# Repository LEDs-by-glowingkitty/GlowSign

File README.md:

## Warning:

This project is currently under active development and has not been fully tested yet. If you decide to build or clone the project, be aware it might not work yet as expected. Use at your own risk.

## What is this project?

A battery powered LED sign for your laptop, or where ever else you want to use it!

## Links

- [Main PCB files](https://github.com/glowingkitty/GlowKittySign/tree/main/Main%20PCB)
- [Aluminum Cover PCB - Cat Edition files](https://github.com/glowingkitty/GlowKittySign/tree/main/AluminumCover%20PCB%20cat%20edition)

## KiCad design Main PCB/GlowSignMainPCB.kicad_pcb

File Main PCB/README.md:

# GlowSign Main PCB

The main PCB for GlowSign. With all the LEDs, the integrated ESP32, a microphone to make the LED animations react to music - and it runs GlowOS (my WLED fork). But you can also upload your own software to the ESP32. The PCB can be powered via USB-C and via a lipo battery.

## Links

- [Schematic](https://github.com/glowingkitty/GlowSign/blob/main/Main%20PCB/GlowSignMainPCB.pdf)
- [Interactive BOM](https://htmlpreview.github.io/?https://github.com/glowingkitty/GlowSign/blob/main/Main%20PCB/bom/ibom.html)

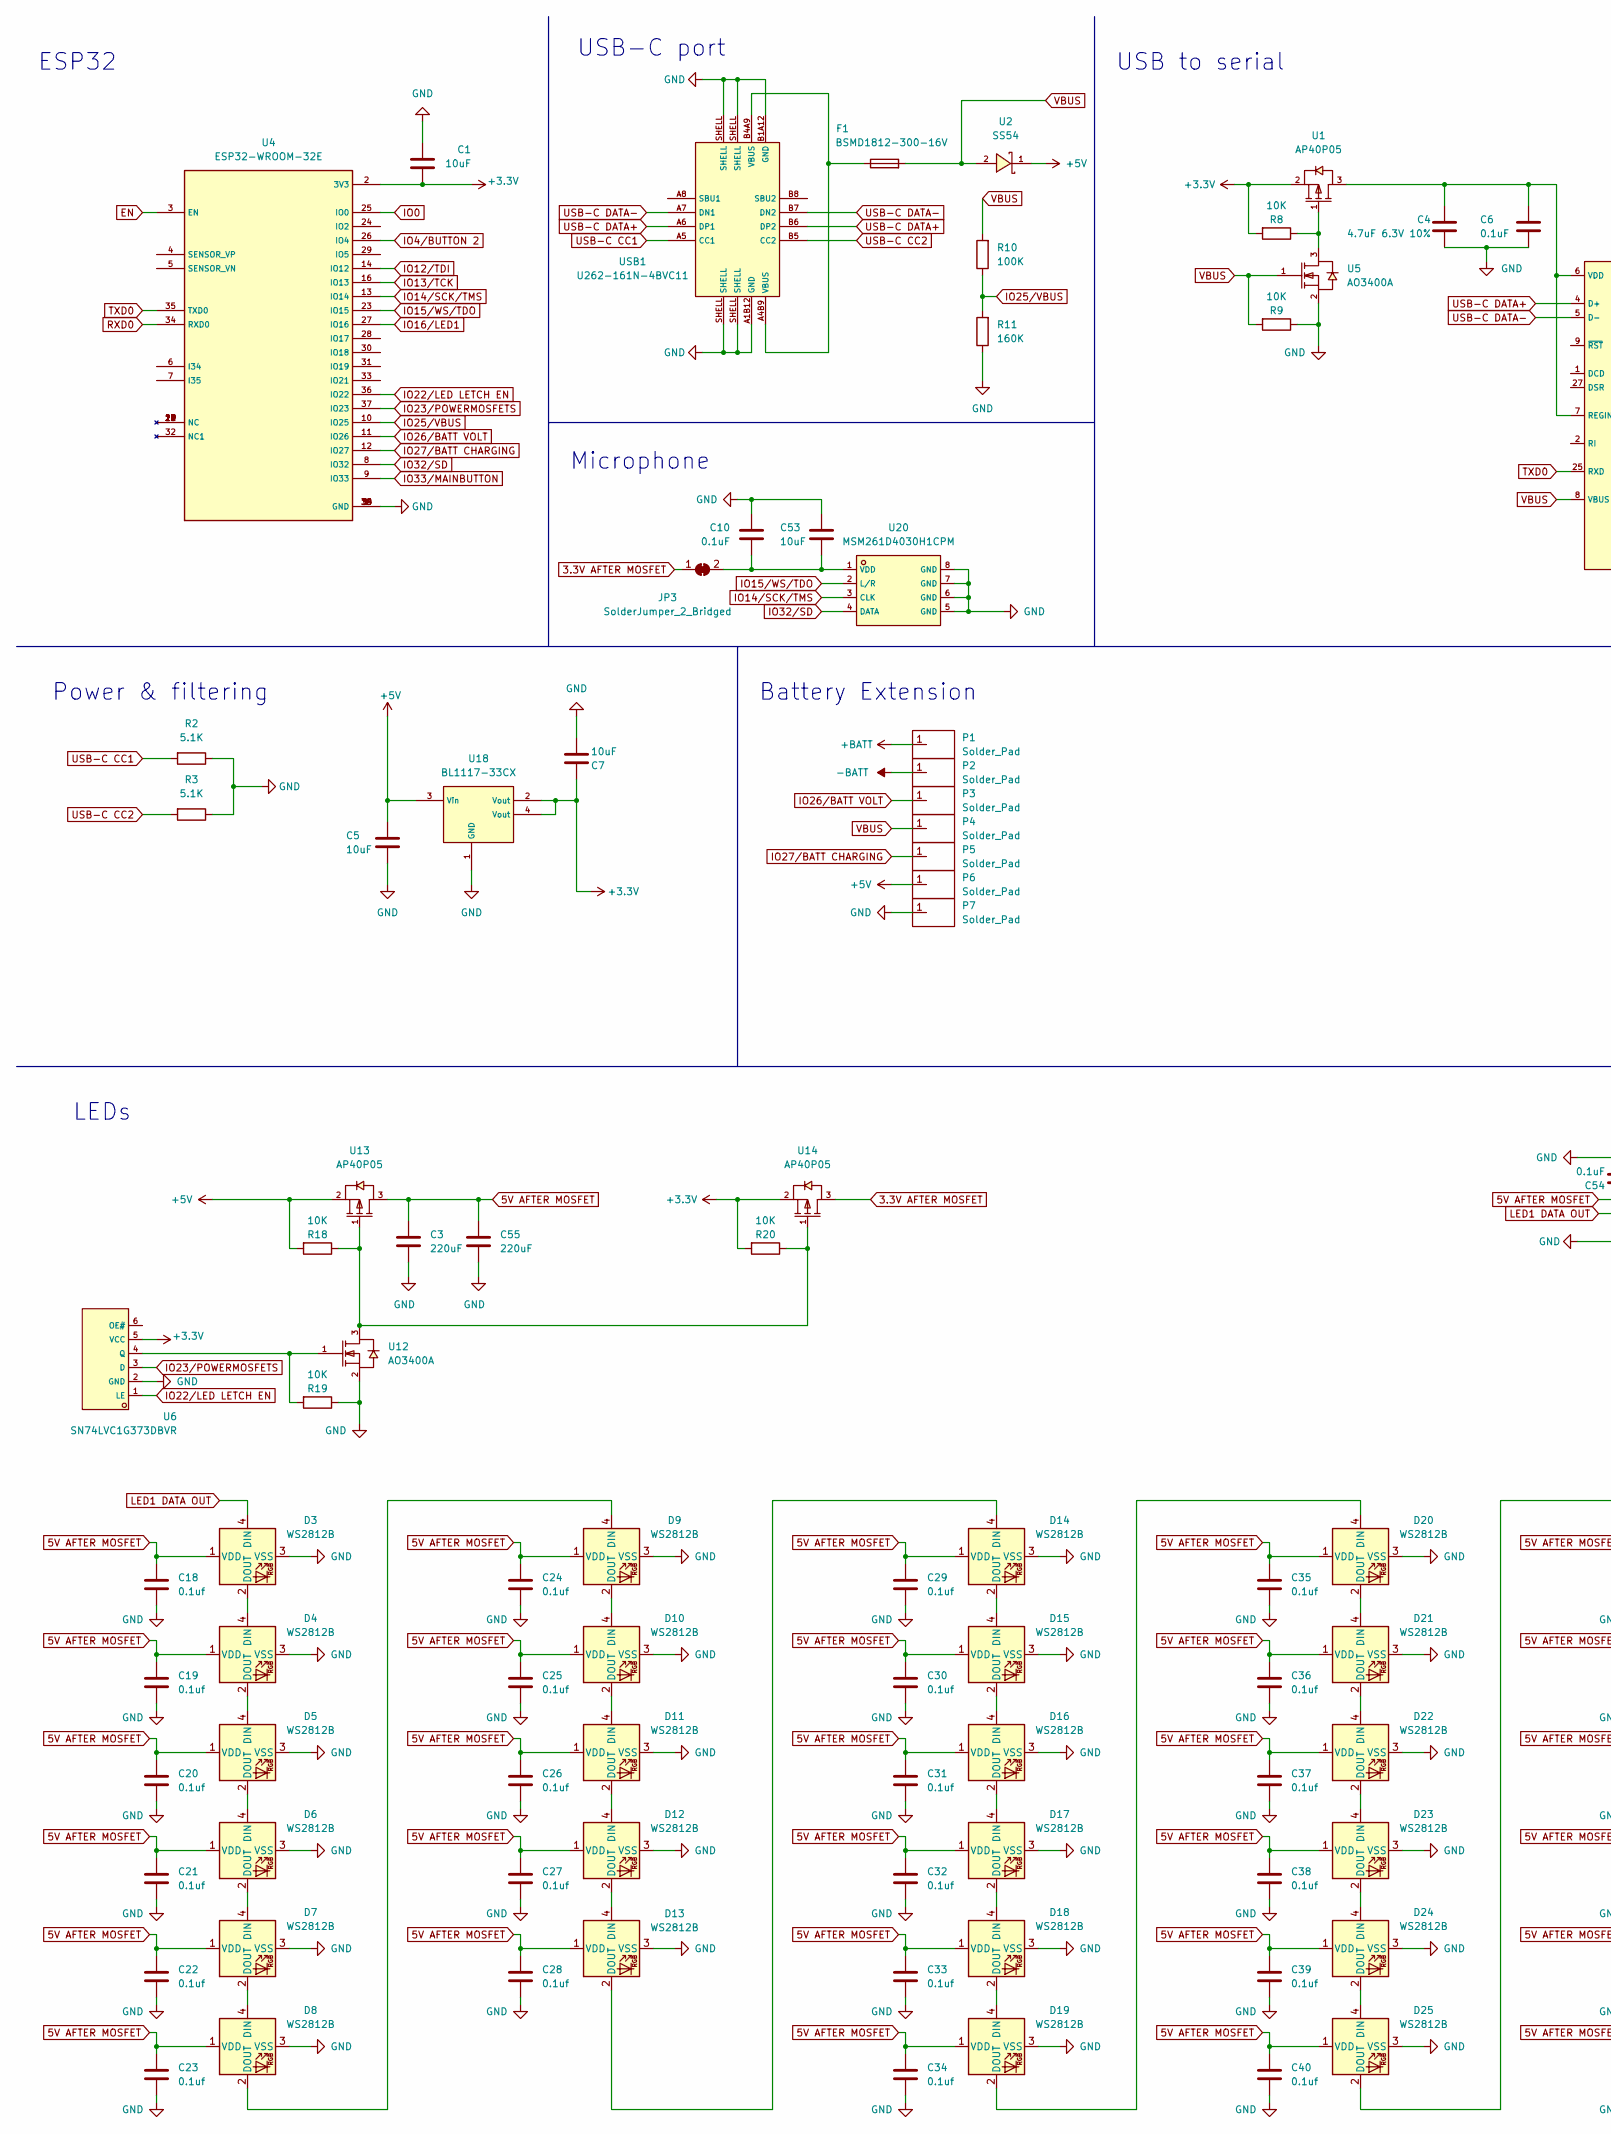
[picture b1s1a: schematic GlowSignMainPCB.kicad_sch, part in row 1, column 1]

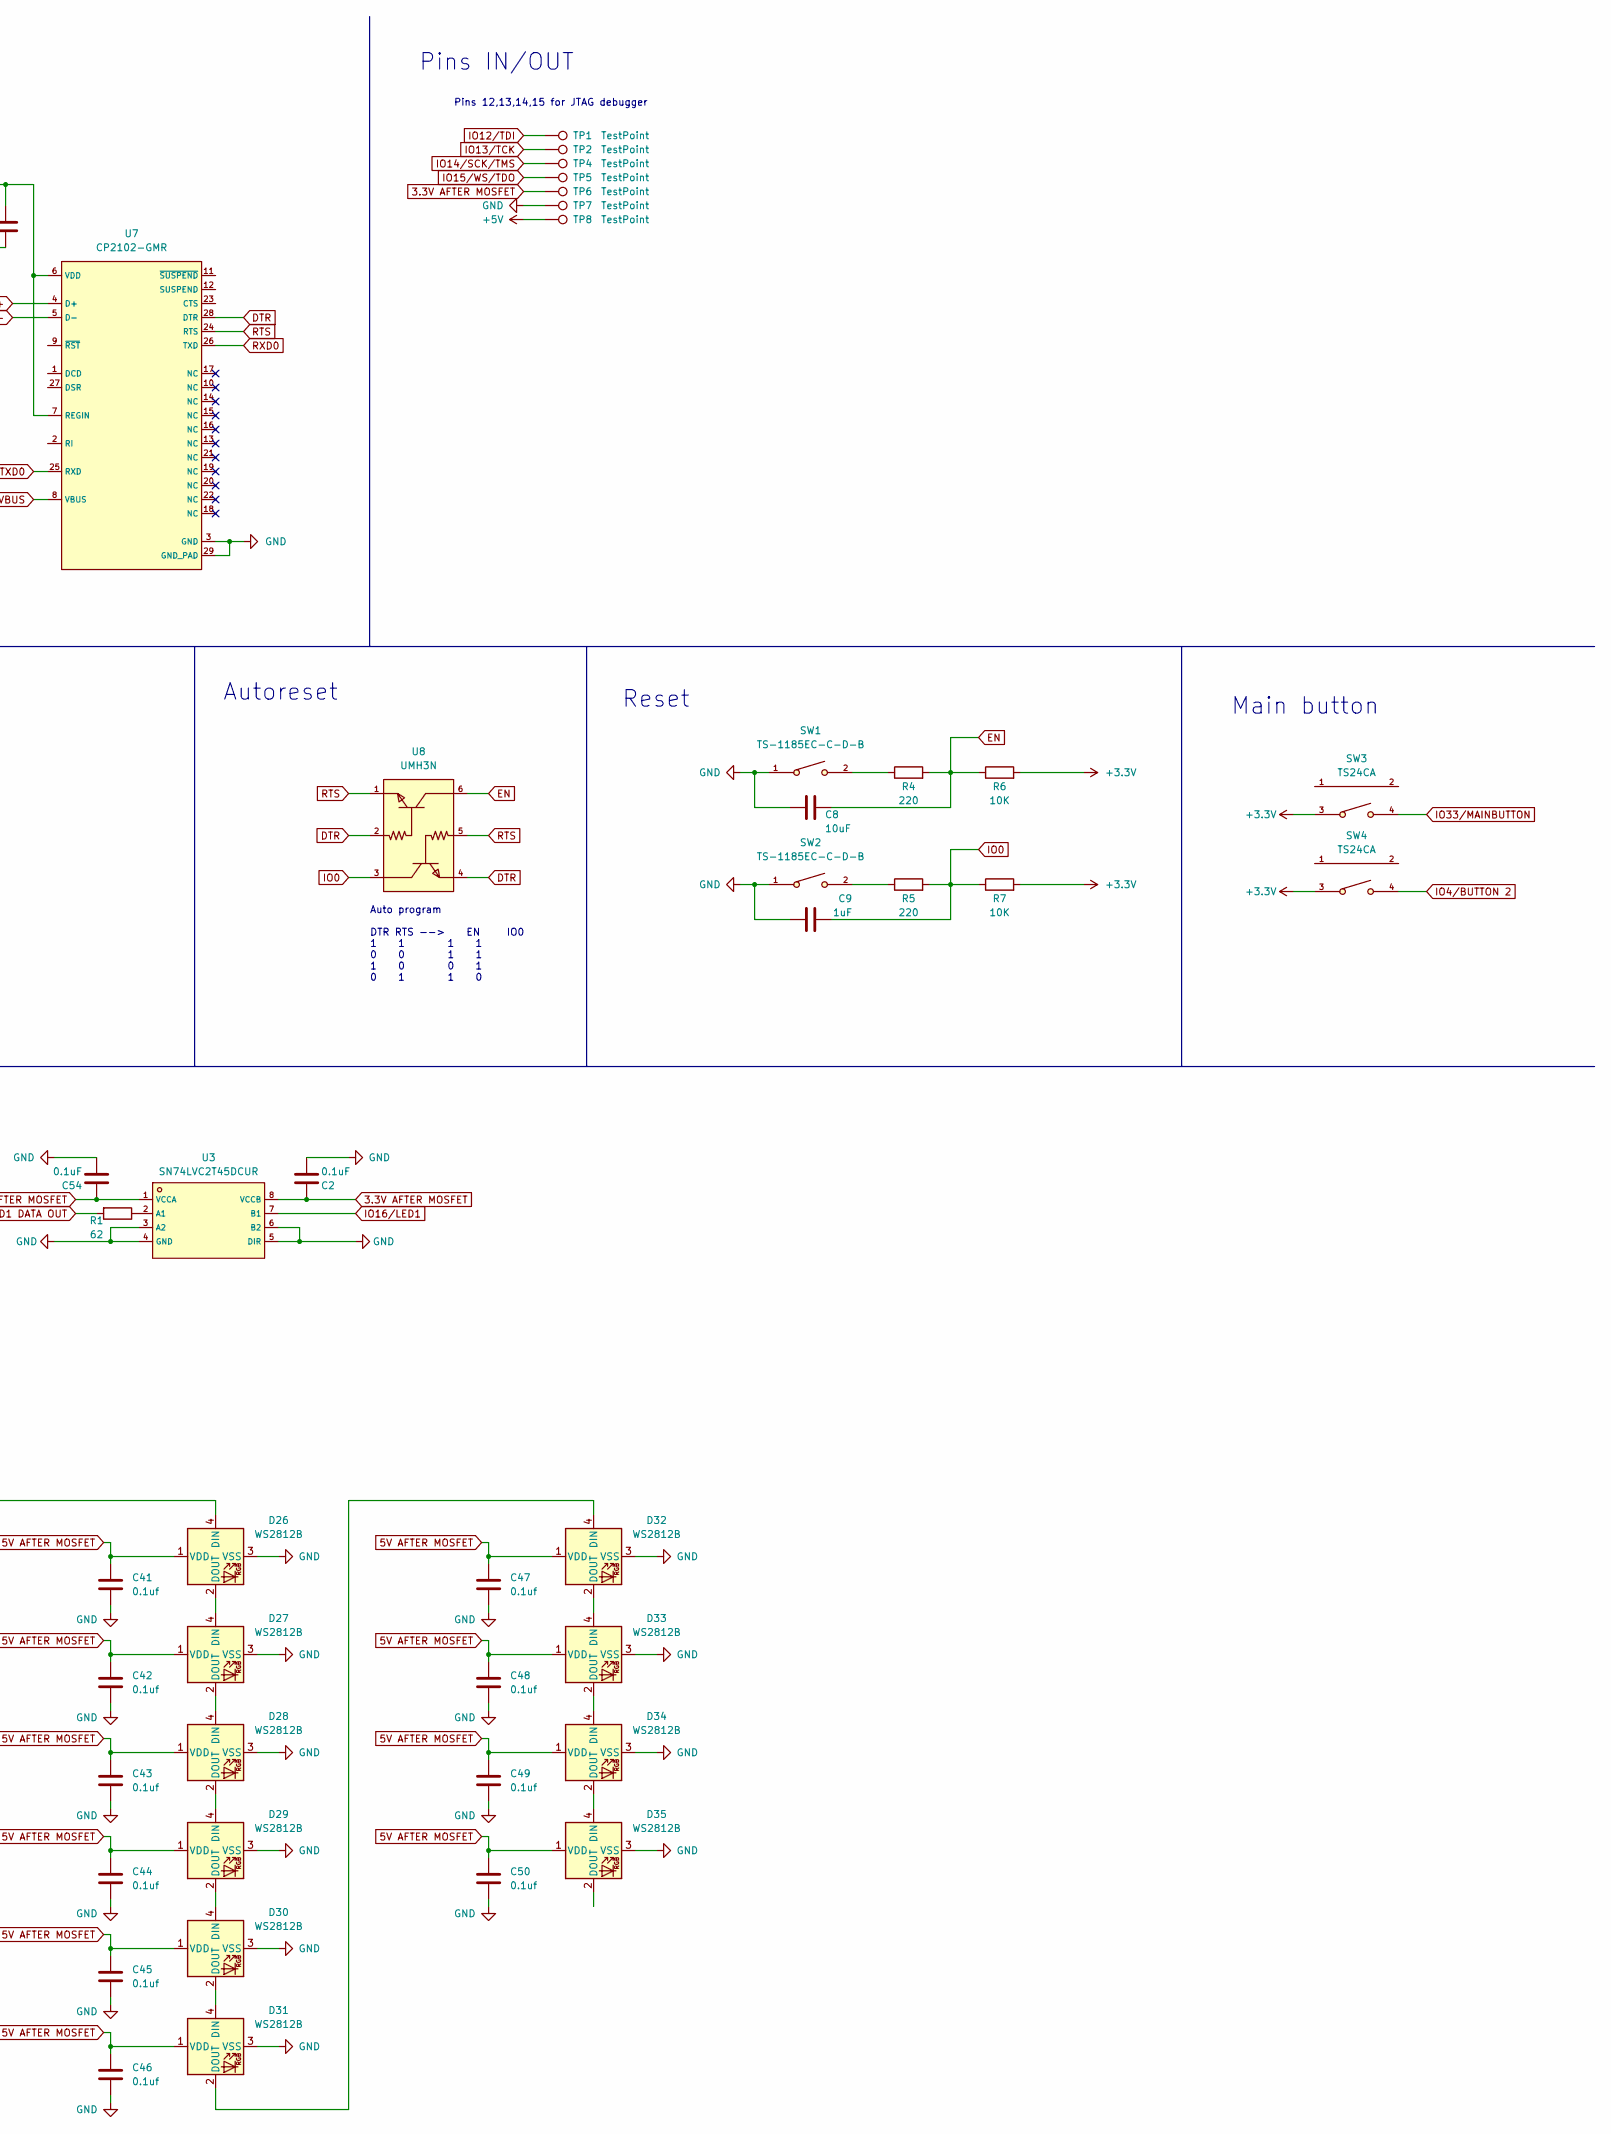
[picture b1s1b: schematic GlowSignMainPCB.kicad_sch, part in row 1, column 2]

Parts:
C1, C5, C7, C8, C53: 10uF; C_0603_1608Metric_Pad1.08x0.95mm_HandSolder; LCSC # C19702
C2, C6, C10, C54: 0.1uF; C_0603_1608Metric_Pad1.08x0.95mm_HandSolder; LCSC # C14663
C3, C55: 220uF; C_1206_3216Metric_Pad1.33x1.80mm_HandSolder; LCSC # C412252
C4: 4.7uF 6.3V 10%; C_0603_1608Metric_Pad1.08x0.95mm_HandSolder; LCSC # C19666
C9: 1uF; C_0603_1608Metric_Pad1.08x0.95mm_HandSolder; LCSC # C15849
C18, C19, C20, C21, C22, C23, C24, C25, C26, C27, C28, C29, C30, C31, C32, C33, C34, C35, C36, C37, C38, C39, C40, C41, C42, C43, C44, C45, C46, C47, C48, C49, C50: 0.1uf; C_0603_1608Metric_Pad1.08x0.95mm_HandSolder; LCSC # C14663
D3, D4, D5, D6, D7, D8, D9, D10, D11, D12, D13, D14, D15, D16, D17, D18, D19, D20, D21, D22, D23, D24, D25, D26, D27, D28, D29, D30, D31, D32, D33, D34, D35: WS2812B; LED_WS2812B_PLCC4_5.0x5.0mm_P3.2mm; LCSC # C2843785
F1: BSMD1812-300-16V; Fuse_1812_4532Metric_Pad1.30x3.40mm_HandSolder; LCSC # C883162
JP3: SolderJumper_2_Bridged; SolderJumper-2_P1.3mm_Bridged_RoundedPad1.0x1.5mm
P1, P2, P3, P4, P5, P6, P7: Solder_Pad; Solder pad
R1: 62; R_0603_1608Metric_Pad0.98x0.95mm_HandSolder; LCSC # C177352
R2, R3: 5.1K; R_0603_1608Metric_Pad0.98x0.95mm_HandSolder; LCSC # C23186
R4, R5: 220; R_0603_1608Metric_Pad0.98x0.95mm_HandSolder; LCSC # C22962
R6, R7, R8, R9, R18, R19, R20: 10K; R_0603_1608Metric_Pad0.98x0.95mm_HandSolder; LCSC # C25804
R10: 100K; R_0603_1608Metric_Pad0.98x0.95mm_HandSolder; LCSC # C25803
R11: 160K; R_0603_1608Metric_Pad0.98x0.95mm_HandSolder; LCSC # C22813
SW1, SW2: TS-1185EC-C-D-B; SW-SMD_4P-L3.7-W3.0-P1.50-LS4.7; LCSC # C318893
SW3, SW4: TS24CA; SW-SMD_TS24CA; LCSC C393942
TP1, TP2, TP4, TP5, TP6, TP7, TP8: TestPoint; TestPoint_Pad_D1.5mm
U1, U13, U14: AP40P05; SOT-23-3_L2.9-W1.3-P1.90-LS2.4-BR; LCSC # C2886385
U2: SS54; SMA_L4.4-W2.8-LS5.4-RD; LCSC # C123946
U3: SN74LVC2T45DCUR; VSSOP-8_L2.4-W2.1-P0.50-LS3.2-BR; LCSC # C15741
U4: ESP32-WROOM-32E; WIFI-SMD_ESP32-WROOM-32E; LCSC # C701341
U5, U12: AO3400A; SOT-23-3_L2.9-W1.6-P1.90-LS2.8-BR; LCSC # C20917
U6: SN74LVC1G373DBVR; SOT-23-6_L2.9-W1.6-P0.95-LS2.8-BR; LCSC C128413
U7: CP2102-GMR; QFN-28_L5.0-W5.0-P0.50-BL-EP; LCSC # C6568
U8: UMH3N; SC-70-6_L2.2-W1.3-P0.65-LS2.1-BR; LCSC # C62892
U18: BL1117-33CX; SOT-223-4_L6.5-W3.5-P2.30-LS7.0-BR; LCSC # C5400
U20: MSM261D4030H1CPM; MIC-SMD_8P-L3.0-W4.0-P0.85-BL; LCSC # C966942
USB1: U262-161N-4BVC11; USB-3.1-SMD_U262-161N-4BVC11; LCSC # C319148

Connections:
3.3V AFTER MOSFET: C2.1, JP3.1 (A), TP6.1, U3.8 (VCCB), U14.3 (D)
5V AFTER MOSFET: C3.1, C18.1, C19.1, C20.1, C21.1, C22.1, C23.1, C24.1, C25.1, C26.1, C27.1, C28.1, C29.1, C30.1, C31.1, C32.1, C33.1, C34.1, C35.1, C36.1, C37.1, C38.1, C39.1, C40.1, C41.1, C42.1, C43.1, C44.1, C45.1, C46.1, C47.1, C48.1, C49.1, C50.1, C54.1, C55.1, D3.1 (VDD), D4.1 (VDD), D5.1 (VDD), D6.1 (VDD), D7.1 (VDD), D8.1 (VDD), D9.1 (VDD), D10.1 (VDD), D11.1 (VDD), D12.1 (VDD), D13.1 (VDD), D14.1 (VDD), D15.1 (VDD), D16.1 (VDD), D17.1 (VDD), D18.1 (VDD), D19.1 (VDD), D20.1 (VDD), D21.1 (VDD), D22.1 (VDD), D23.1 (VDD), D24.1 (VDD), D25.1 (VDD), D26.1 (VDD), D27.1 (VDD), D28.1 (VDD), D29.1 (VDD), D30.1 (VDD), D31.1 (VDD), D32.1 (VDD), D33.1 (VDD), D34.1 (VDD), D35.1 (VDD), U3.1 (VCCA), U13.3 (D)
+3V3: C1.2, C7.2, R6.2, R7.2, R8.2, R20.2, SW3.3, SW4.3, U1.2 (S), U4.2 (3V3), U6.5 (VCC), U14.2 (S), U18.2 (Vout), U18.4 (Vout)
+5V: C5.2, P6.1, R18.2, TP8.1, U2.1 (K), U13.2 (S), U18.3 (Vin)
+BATT: P1.1
-BATT: P2.1
DTR: U7.28 (DTR), U8.2 (B), U8.4 (E)
EN: C8.2, R4.2, R6.1, U4.3 (EN), U8.6 (C)
GND: C1.1, C2.2, C3.2, C4.1, C5.1, C6.2, C7.1, C8.1, C9.2, C10.1, C18.2, C19.2, C20.2, C21.2, C22.2, C23.2, C24.2, C25.2, C26.2, C27.2, C28.2, C29.2, C30.2, C31.2, C32.2, C33.2, C34.2, C35.2, C36.2, C37.2, C38.2, C39.2, C40.2, C41.2, C42.2, C43.2, C44.2, C45.2, C46.2, C47.2, C48.2, C49.2, C50.2, C53.1, C54.2, C55.2, D3.3 (VSS), D4.3 (VSS), D5.3 (VSS), D6.3 (VSS), D7.3 (VSS), D8.3 (VSS), D9.3 (VSS), D10.3 (VSS), D11.3 (VSS), D12.3 (VSS), D13.3 (VSS), D14.3 (VSS), D15.3 (VSS), D16.3 (VSS), D17.3 (VSS), D18.3 (VSS), D19.3 (VSS), D20.3 (VSS), D21.3 (VSS), D22.3 (VSS), D23.3 (VSS), D24.3 (VSS), D25.3 (VSS), D26.3 (VSS), D27.3 (VSS), D28.3 (VSS), D29.3 (VSS), D30.3 (VSS), D31.3 (VSS), D32.3 (VSS), D33.3 (VSS), D34.3 (VSS), D35.3 (VSS), P7.1, R2.1, R3.1, R9.1, R11.1, R19.1, SW1.1, SW2.1, TP7.1, U3.3 (A2), U3.4 (GND), U3.5 (DIR), U3.6 (B2), U4.1 (GND), U4.15 (GND), U4.38 (GND), U4.39 (GND), U5.2 (S), U6.2 (GND), U7.3 (GND), U7.29 (GND_PAD), U12.2 (S), U18.1 (GND), U20.5 (GND), U20.6 (GND), U20.7 (GND), U20.8 (GND), USB1.A1B12 (GND), USB1.B1A12 (GND), USB1.SHELL
IO0: C9.1, R5.2, R7.1, U4.25 (IO0), U8.3 (C)
IO4/BUTTON 2: SW4.4, U4.26 (IO4)
IO12/TDI: TP1.1, U4.14 (IO12)
IO13/TCK: TP2.1, U4.16 (IO13)
IO14/SCK/TMS: TP4.1, U4.13 (IO14), U20.3 (CLK)
IO15/WS/TDO: TP5.1, U4.23 (IO15), U20.2 (L/R)
IO16/LED1: U3.7 (B1), U4.27 (IO16)
IO22/LED LETCH EN: U4.36 (IO22), U6.1 (LE)
IO23/POWERMOSFETS: U4.37 (IO23), U6.3 (D)
IO25/VBUS: R10.1, R11.2, U4.10 (IO25)
IO26/BATT VOLT: P3.1, U4.11 (IO26)
IO27/BATT CHARGING: P5.1, U4.12 (IO27)
IO32/SD: U4.8 (IO32), U20.4 (DATA)
IO33/MAINBUTTON: SW3.4, U4.9 (IO33)
LED1 DATA OUT: D3.4 (DIN), R1.2
unnamed: C4.2, C6.1, U1.3 (D), U7.6 (VDD), U7.7 (REGIN)
unnamed: C10.2, C53.2, JP3.2 (B), U20.1 (VDD)
unnamed: D3.2 (DOUT), D4.4 (DIN)
unnamed: D4.2 (DOUT), D5.4 (DIN)
unnamed: D5.2 (DOUT), D6.4 (DIN)
unnamed: D6.2 (DOUT), D7.4 (DIN)
unnamed: D7.2 (DOUT), D8.4 (DIN)
unnamed: D8.2 (DOUT), D9.4 (DIN)
unnamed: D10.2 (DOUT), D11.4 (DIN)
unnamed: D9.2 (DOUT), D10.4 (DIN)
unnamed: D11.2 (DOUT), D12.4 (DIN)
unnamed: D12.2 (DOUT), D13.4 (DIN)
unnamed: D13.2 (DOUT), D14.4 (DIN)
unnamed: D14.2 (DOUT), D15.4 (DIN)
unnamed: D15.2 (DOUT), D16.4 (DIN)
unnamed: D16.2 (DOUT), D17.4 (DIN)
unnamed: D17.2 (DOUT), D18.4 (DIN)
unnamed: D18.2 (DOUT), D19.4 (DIN)
unnamed: D19.2 (DOUT), D20.4 (DIN)
unnamed: D20.2 (DOUT), D21.4 (DIN)
unnamed: D21.2 (DOUT), D22.4 (DIN)
unnamed: D22.2 (DOUT), D23.4 (DIN)
unnamed: D23.2 (DOUT), D24.4 (DIN)
unnamed: D24.2 (DOUT), D25.4 (DIN)
unnamed: D25.2 (DOUT), D26.4 (DIN)
unnamed: D26.2 (DOUT), D27.4 (DIN)
unnamed: D27.2 (DOUT), D28.4 (DIN)
unnamed: D28.2 (DOUT), D29.4 (DIN)
unnamed: D29.2 (DOUT), D30.4 (DIN)
unnamed: D30.2 (DOUT), D31.4 (DIN)
unnamed: D31.2 (DOUT), D32.4 (DIN)
unnamed: D32.2 (DOUT), D33.4 (DIN)
unnamed: D33.2 (DOUT), D34.4 (DIN)
unnamed: D34.2 (DOUT), D35.4 (DIN)
unnamed: F1.1, USB1.A4B9 (VBUS), USB1.B4A9 (VBUS)
unnamed: R1.1, U3.2 (A1)
unnamed: R4.1, SW1.2
unnamed: R5.1, SW2.2
unnamed: R8.1, U1.1 (G), U5.3 (D)
unnamed: R18.1, R20.1, U12.3 (D), U13.1 (G), U14.1 (G)
unnamed: R19.2, U6.4 (Q), U12.1 (G)
RTS: U7.24 (RTS), U8.1 (E), U8.5 (B)
RXD0: U4.34 (RXD0), U7.26 (TXD)
TXD0: U4.35 (TXD0), U7.25 (RXD)
USB-C CC1: R2.2, USB1.A5 (CC1)
USB-C CC2: R3.2, USB1.B5 (CC2)
USB-C DATA+: U7.4 (D+), USB1.A6 (DP1), USB1.B6 (DP2)
USB-C DATA-: U7.5 (D-), USB1.A7 (DN1), USB1.B7 (DN2)
VBUS: F1.2, P4.1, R9.2, R10.2, U2.2 (A), U5.1 (G), U7.8 (VBUS)

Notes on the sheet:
Auto program DTR RTS --> EN IO0 1 1 1 1 0 0 1 1 1 0 0 1 0 1 1 0
Autoreset
USB to serial
Reset
USB-C port
Power & filtering
Pins 12,13,14,15 for JTAG debugger
Main button
ESP32
Battery Extension
LEDs
Microphone
Pins IN/OUT

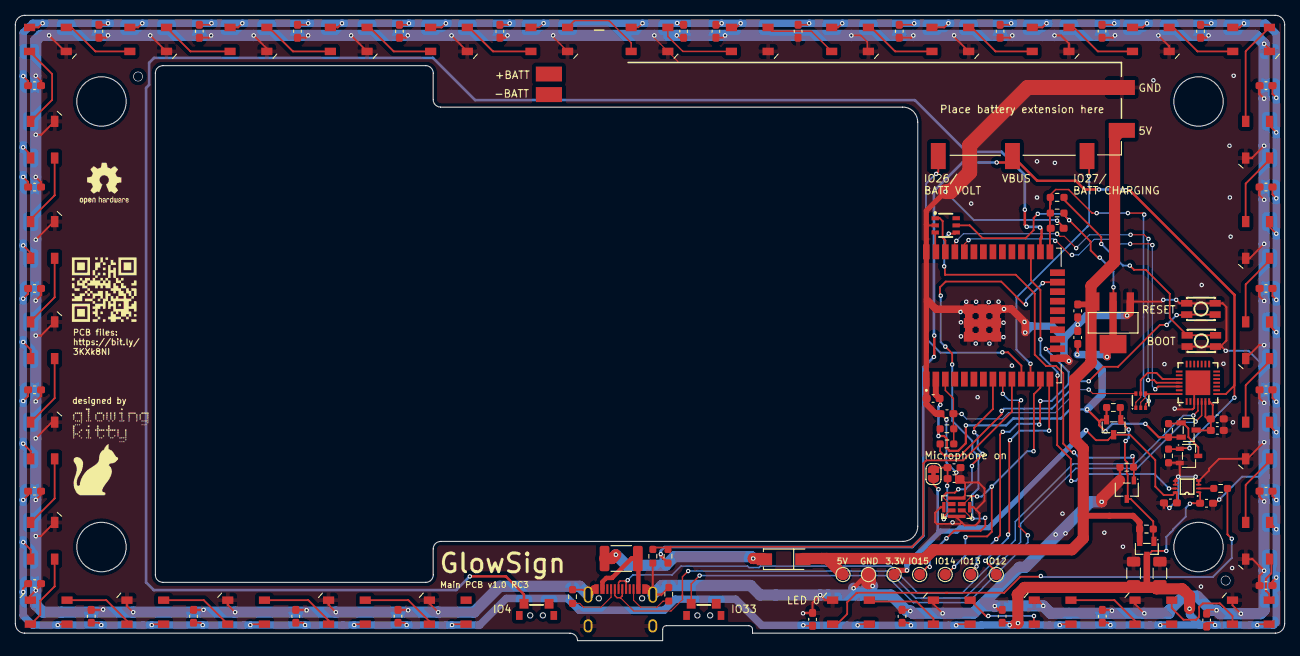
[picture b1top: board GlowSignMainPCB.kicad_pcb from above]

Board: 2 copper layers, 169.5 x 83.5 mm, 130 parts (0 on the bottom side), 71 nets.

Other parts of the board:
OSHW logo: OSHW-Logo2_7.3x6mm_SilkScreen
logo: LOGO
qrcode: LOGO

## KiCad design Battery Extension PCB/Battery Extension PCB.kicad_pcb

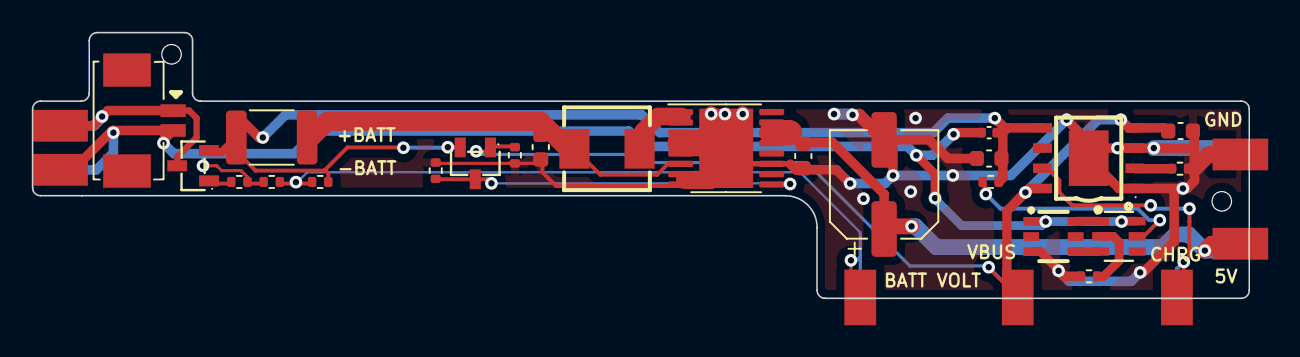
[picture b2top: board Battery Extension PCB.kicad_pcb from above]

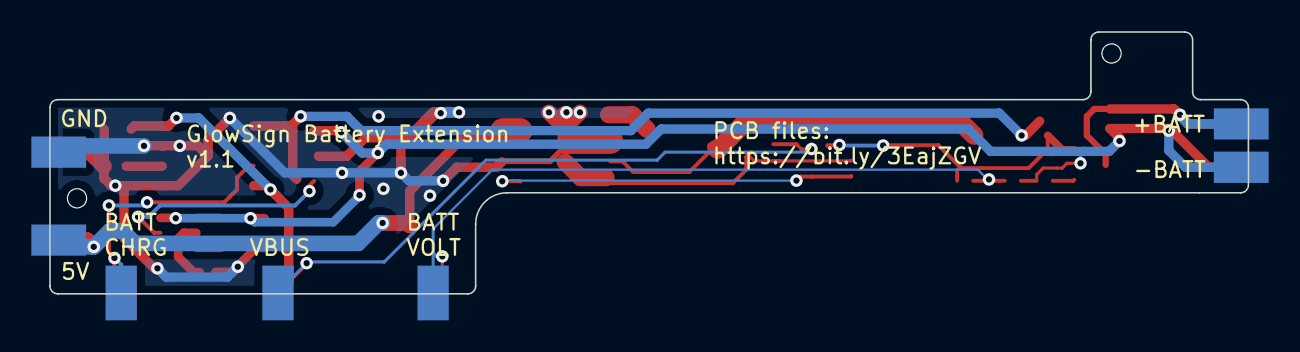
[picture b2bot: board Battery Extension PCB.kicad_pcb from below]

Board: 2 copper layers, 76.5 x 16.7 mm, 37 parts (7 on the bottom side), 17 nets.

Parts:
C1, C2, C4: 10uF; C_0603_1608Metric
C3: 2.2uF; C_0603_1608Metric
C5: 0.1uF; C_0402_1005Metric
C6: 220uF 10V; CP_Elec_6.3x5.4
F1: BSMD1812-300-16V; Fuse_1812_4532Metric_Pad1.30x3.40mm_HandSolder
P1, P2, P3, P4, P5, P6, P7, P8, P9, P10, P11, P12, P13, P14: Solder_Pad; Solder pad
R1: 33K; R_0402_1005Metric
R2, R3, R6, R9: 100K; R_0402_1005Metric
R5: 1K; R_0402_1005Metric
R7: 2K; R_0402_1005Metric
R8: 100; R_0402_1005Metric
U1: M1250RS-02P; CONN-SMD_2P-P1.25_L4.4-W7.4
U2, U8: AP40P05; SOT-23-3_L2.9-W1.3-P1.90-LS2.4-BR
U3: FS8205A; SOT-23-6_L2.9-W1.6-P0.95-LS2.8-BR
U4: TPS61032PWPR; HTSSOP-16-1EP_4.4x5mm_P0.65mm_EP3.4x5mm_Mask2.46x2.31mm
U5: TP4056; ESOP-8_L4.9-W3.9-P1.27-LS6.0-BL-EP
U6: DW01A; SOT-23-6_L2.9-W1.6-P0.95-LS2.8-BL
U7: FXL0530-6R8-M; IND-SMD_L5.4-W5.2_FXL0530

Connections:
+5V: C3.2, C6.1, P5.1, P12.1, U4.13 (VOUT), U4.14 (VOUT), U4.15 (VOUT)
+BATT: C4.1, C5.2, F1.1, R1.2, R8.2, U2.2 (S), U5.5 (BAT), U8.2 (S)
-BATT: C5.1, P2.1, P9.1, R2.1, R3.1, U1.2, U3.1 (S1), U6.6 (GND)
BATT CHARGING: P4.1, P11.1, U5.7 (CHRG#)
BATT VOLT: P3.1, P10.1, R1.1, R2.2
GND: C1.1, C2.2, C3.1, C4.2, C6.2, P6.1, P13.1, R5.1, R6.2, R7.2, R9.2, U3.3 (S2), U4.3 (PGND), U4.4 (PGND), U4.5 (PGND), U4.7 (LBI), U4.8 (SYNC), U4.11 (GND), U4.17 (EP), U5.1 (TEMP), U5.3 (GND), U5.9 (EP)
unnamed: C2.1, F1.2, U4.6 (VBAT), U7.1
unnamed: P1.1, P8.1, U1.1, U2.3 (D)
unnamed: R3.2, U2.1 (G)
unnamed: R5.2, U6.2 (VM)
unnamed: R7.1, U5.2 (PROG)
unnamed: R8.1, U6.5 (VCC)
unnamed: R9.1, U4.9 (EN), U8.3 (D)
unnamed: U3.4 (G2), U6.3 (OC)
unnamed: U3.6 (G1), U6.1 (OD)
unnamed: U4.1 (SW), U4.2 (SW), U7.2
VBUS: C1.2, P7.1, P14.1, R6.1, U5.4 (VCC), U5.8 (CE), U8.1 (G)

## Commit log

2022-05-06 added pcb files (in dev)
2022-05-10 completed first prototype
2022-05-10 fixed link
2022-05-10 fixed name
2022-05-13 updated lasercut stencils
2022-06-04 updated mic and levelshifter
2022-07-10 made improvements and started creating usb-c only version
2022-08-06 added new glowsign design
2022-08-06 added qr code to cover pcb square
2022-08-06 updated cover circle pcb
2022-08-06 update images
2022-08-06 updated schematic
2022-08-06 update image
2022-08-10 fixed important mistake... VBUS not connected...
2022-08-24 created stencil, updated acrylic plate cutout
2022-09-08 separated battery electronics into separate pcb
2022-09-09 updated pcb files
2022-09-10 replaced castallated holes with solder pads
2022-09-10 updated pcb
2022-10-02 fixed battery extension
2022-10-02 cleared folders
2022-10-05 replaced 0603 with 0402 (battery extension)
2022-10-05 fixed schematic naming
2022-11-02 updated pcb designs
2022-11-09 fixed deep sleep power consumption + new LED0
2022-11-26 updated case design
2022-12-03 added pinout
2022-12-04 update pinout naming
2022-12-04 added pinout legend
2022-12-04 added pinout pdf
2022-12-05 updated pinout
2022-12-06 added pdf qr code to pinout
